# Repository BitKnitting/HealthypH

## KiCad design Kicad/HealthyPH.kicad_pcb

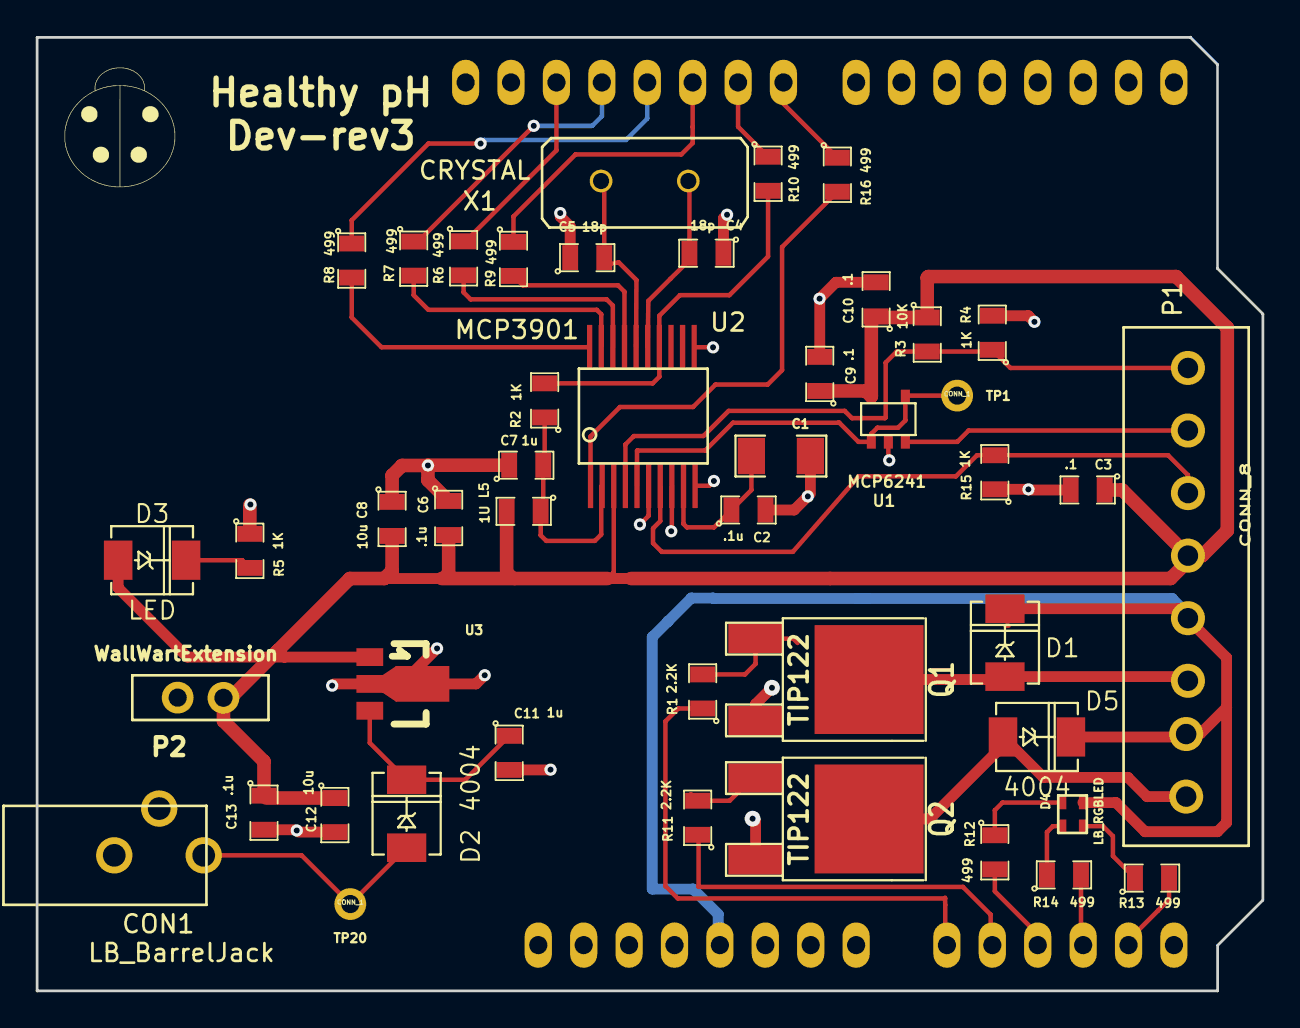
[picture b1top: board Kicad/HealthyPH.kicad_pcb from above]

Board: 2 copper layers, 68.6 x 53.4 mm, 46 parts (0 on the bottom side), 28 nets.

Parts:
C1: 10u; SM1206
C2, C6, C13: .1u; SM0805
C3, C9, C10: .1; SM0805
C4, C5: 18p; SM0805
C7, C11: 1u; SM0805
C8, C12: 10u; SM0805
CON1: LB_BarrelJack; LB_BarrelJack_Correct
D1: DO-214AC(SMA)
D2, D5: 4004; DO-214AC(SMA)
D3: LED; DO-214AC(SMA)
D4: LB_RGBLED
L5: 1U; SM0805
P1: CONN_8; LB_8PosTB
P2: WallWartExtension; LB_2TB
Q1, Q2: TIP122; DPAK2
R1, R11: 2.2K; SM0805
R2, R4, R5, R15: 1K; SM0805
R3: 10K; SM0805
R6, R7, R8, R9, R10, R12, R13, R14, R16: 499; SM0805
TP1, TP20: CONN_1; LB_TestPoint
U1: MCP6241; SOT23-5
U2: MCP3901; LB_MCP3901
U3: MC78L05; LB_SOT89_3
X1: CRYSTAL; LB_Crystal

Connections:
/Arduino/V+_ARD: D1.2, D4.4, D5.2, P1.5, P1.7
/Digital Access/MISO_ISO: R7.2, U2.19
/Digital Access/MOSI_ISO: R8.2, U2.20
/Digital Access/SCLK_ISO: R6.2, U2.18
/Digital Access/V+_WallWart: C3.1, C6.2, C8.2, C9.1, C10.1, C12.1, C13.1, D3.1, L5.2, P1.4, P2.2, R3.1, U1.5, U2.3, U3.1
/Digital Access/pH_ADC+: TP1.1, U1.1, U1.4, U2.5
/Digital Access/pH_ADC-: P1.1, R3.2, R4.1, U2.4
/Digital Access/~CS_ISO: R9.2, U2.17
/Digital Access/~DR: R2.2, R10.2, U2.14
/Digital Access/~RESET: R16.2, U2.1
/Pumps/SW_DownPump: D1.1, P1.6, Q1.2
/Pumps/SW_UpPump: D5.1, P1.8, Q2.2
/Temperature/10K Therm: P1.3, R15.2, U2.7
/pH/pH_Probe_V: P1.2, U1.3
AGND: C1.2, C2.2, C3.2, C4.1, C5.1, C6.1, C7.1, C8.1, C9.2, C10.2, C11.2, C12.2, C13.2, CON1.2, CON1.3, P2.1, R4.2, R5.1, R15.1, U1.2, U2.6, U2.8, U2.10, U2.11, U3.2
GND: Q1.3, Q2.3
unnamed: Q2.1, R11.2
unnamed: Q1.1, R1.2
unnamed: C5.2, U2.16, X1.1
unnamed: C4.2, U2.15, X1.2
unnamed: C7.2, L5.1, R2.1, U2.2
unnamed: C1.1, C2.1, U2.9
unnamed: C11.1, D2.2, U3.3
unnamed: CON1.1, D2.1, TP20.1
unnamed: D3.2, R5.2
unnamed: D4.2, R14.1
unnamed: D4.1, R12.1
unnamed: D4.3, R13.1

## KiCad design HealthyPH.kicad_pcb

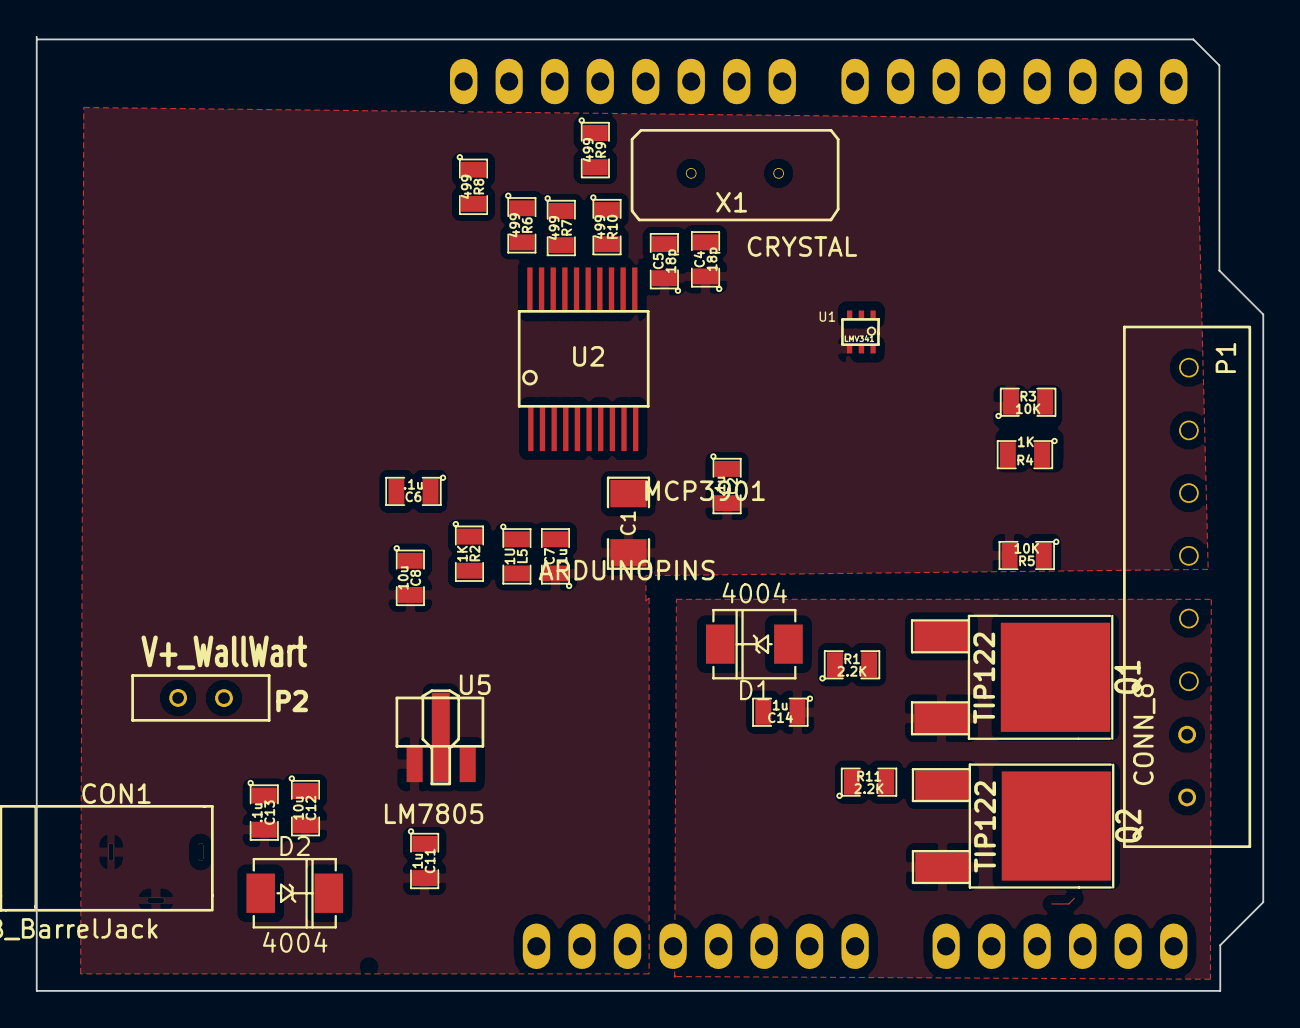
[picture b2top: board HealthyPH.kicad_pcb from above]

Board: 2 copper layers, 68.4 x 53.2 mm, 35 parts (0 on the bottom side), 23 nets.

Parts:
ARD1: ARDUINOPINS; ArduinoLettuceBuddy
C1: 10u; SM1206
C2, C6, C13: .1u; SM0805
C4, C5: 18p; SM0805
C7, C11, C14: 1u; SM0805
C8, C12: 10u; SM0805
CON1: LB_BarrelJack
D1, D2: 4004; DO-214AC(SMA)
L5: 1U; SM0805
P1: CONN_8; LB_8PosTB
P2: V+_WallWart; LB_2TB
Q1, Q2: TIP122; DPAK2
R1, R11: 2.2K; SM0805
R2, R4: 1K; SM0805
R3, R5: 10K; SM0805
R6, R7, R8, R9, R10: 499; SM0805
U1: LMV341; LB_LMV341
U2: MCP3901; LB_MCP3901
U5: LM7805; LB_SOT89
X1: CRYSTAL; LB_Crystal

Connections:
+5V: C6.1, C7.2, C12.1, C13.1, L5.1, L5.2, P1.3, P2.1, P2.2, R2.1, R2.2, R10.2, U2.2, U2.3, U2.14, U5.2
/Arduino/PumpUp: ARD1.6, R11.1
/Arduino/V+_ARD: ARD1.1, C14.2, D1.2
/Digital Access/MISO_ISO: R7.2, U2.19
/Digital Access/MOSI_ISO: R8.2, U2.20
/Digital Access/OSC1: C4.2, U2.15, X1.2
/Digital Access/OSC2: C5.2, U2.16, X1.1
/Digital Access/RFIN+: C1.1, C2.1, U2.9
/Digital Access/SCLK_ISO: R6.2, U2.18
/Digital Access/pH_ADC+: P1.2, R3.2, R4.1, U1.2, U1.3, U2.4, U2.5
/Digital Access/~CS_ISO: R9.2, U2.17
/Pumps/DownPump: ARD1.5, R1.1
/Pumps/PUMP: Q1.1, Q2.1, R1.2, R11.2
/Pumps/SW_DownPump: P1.6, Q1.2
/Pumps/SW_UpPump: P1.8, Q2.2
/Pumps/V+_DownPump: D1.1, P1.5, P1.7
/Temperature/Temp: P1.4, R5.1, U2.7
/Wall Wart/Vin: C11.1, CON1.1, D2.1, D2.2, U5.3
/pH/V+_WallWart: R3.1, U1.6
/pH/pH_V+(in): P1.1, U1.1
AGND: C1.2, C2.2, C4.1, C5.1, C7.1, C8.2, C11.2, C12.2, C13.2, CON1.2, CON1.3, R4.2, R5.2, U1.4, U2.6, U2.8, U2.11, U5.1
GND: ARD1.2, C14.1, Q1.3, Q2.3
unnamed: C6.2, C8.1

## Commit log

2014-08-12 added 2nd pump in circuit to accomodate pH UP
2014-08-14 changed op amp from LMV341 to MCP6241
2014-08-18 new push
2014-08-19 Layout with traces - ran through ERC and DRC
2014-08-20 updates to layout based on DRC/DFM checks
2014-08-20 Updated layout - no DRC or DFM issues
2014-08-20 increased spoke width around GND pin
2014-08-21 Dev Rev 1
2014-09-09 updates for dev rev 2
2014-09-10 Ready for Schematic Design Review
2014-09-11 updated 500R to 499R
2014-09-14 Layout ready for final check prior to PCB fab
2014-09-14 forgot to update Gerbers. Updated now
2014-09-14 added PDF of BoM
2014-09-15 layout sent to OshPark
2014-09-23 adding diagnostic tests (firmware)
2014-09-24 SPI diagnostics test ready
2014-09-24 RGB LED diag test available
2014-09-24 added turning LED off to diag tests
2014-10-01 updated to include SPI tests
2014-10-01 updated SPI tests - removed older tests
2014-10-03 added average and STDEV to ADC reading
2014-10-04 added test for pumps
2014-10-12 updated with changes for pH volt testing in mcp3901
2014-10-18 Ready for Rev3 First layout review
2014-10-21 updated based on feedback. Ready for second review
2014-11-02 added Processing files for writing from Serial to text file
2014-11-02 upload Processing files
2014-11-11 before changing ADC
2014-11-11 first pass changing ADC
2014-11-13 prior to using Arduino ADC
2014-11-25 changed to mcp3221 - not complete
